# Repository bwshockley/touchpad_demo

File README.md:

# TouchPad Demo
Demo circuit board for vairous electrical touch pads.

# Why?
This is a very simple board meant to provide different methods for creating touch pads on circuit boards using various manufacturing methods via OSH Park (https://oshpark.com).

# Usage
Feel free to use or modify as you like.  Please do not sell this.

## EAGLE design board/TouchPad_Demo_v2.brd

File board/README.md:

# Eagle Files
Eagle files for schematic and the board.

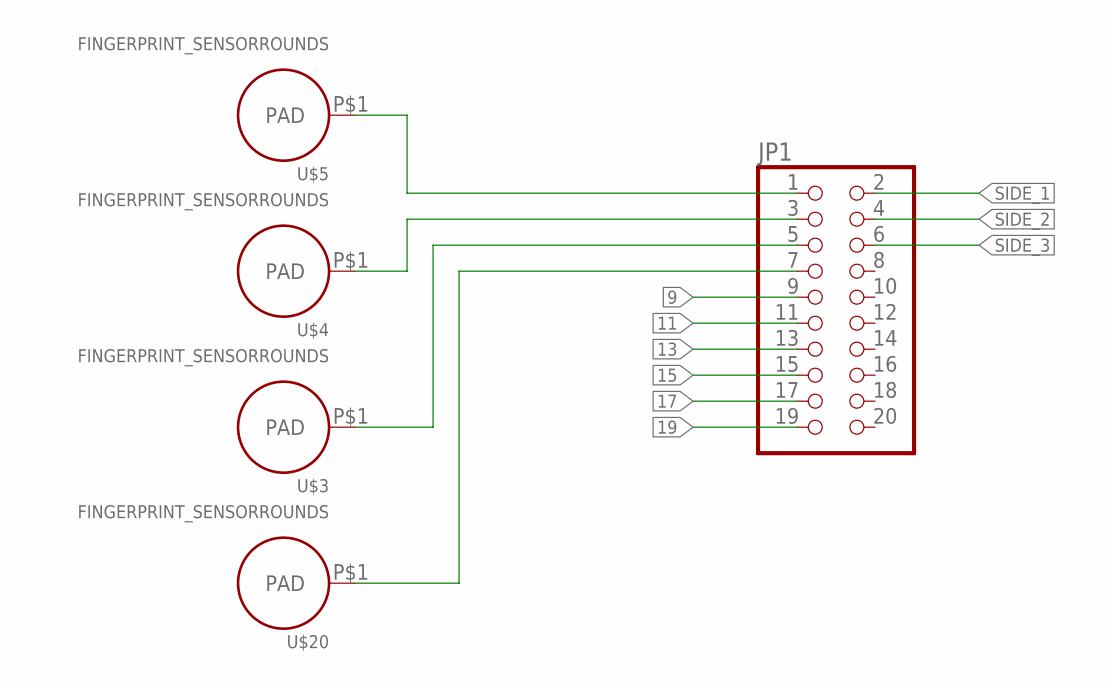
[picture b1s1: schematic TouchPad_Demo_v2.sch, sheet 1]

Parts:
JP1: HEADER-2X10MOLEX20_SIDE; MOLEX20_RIGHTANGLE
U$3, U$4, U$5, U$20: FINGERPRINT_SENSORROUNDS; FINGERPRINT_SENSOR_ROUND

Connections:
9: JP1.9
11: JP1.11
13: JP1.13
15: JP1.15
17: JP1.17
19: JP1.19
unnamed: JP1.1, U$5.P$1
unnamed: JP1.3, U$4.P$1
unnamed: JP1.5, U$3.P$1
unnamed: JP1.7, U$20.P$1
SIDE_1: JP1.2
SIDE_2: JP1.4
SIDE_3: JP1.6

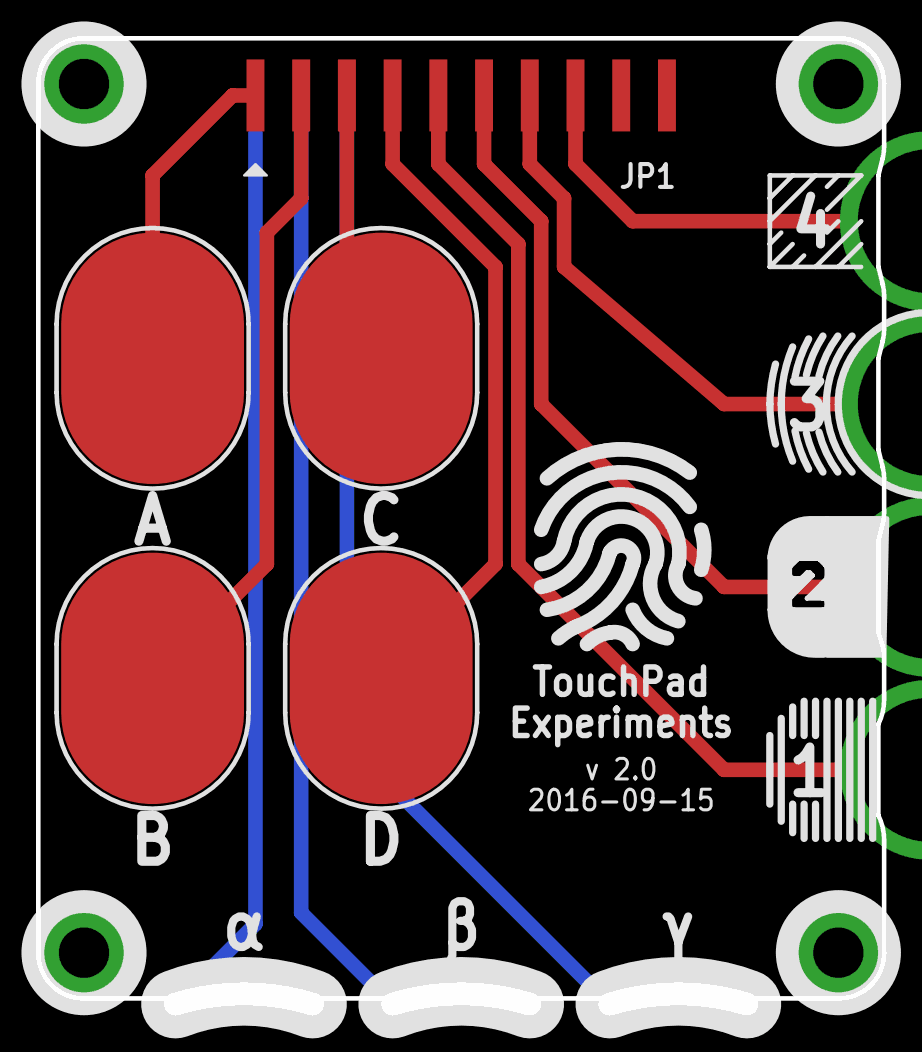
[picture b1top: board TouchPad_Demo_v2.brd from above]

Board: 2 copper layers, 46.0 x 53.1 mm, 7 parts (1 on the bottom side), 4 nets.

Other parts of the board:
U$1, U$19: FINGERPRINT

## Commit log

2016-09-16 Add v2 Schematic and Board

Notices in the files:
parts and their libraries:
microbuilder: This work is placed in the public domain, and may be freely used for commercial and non-commercial work with the following conditions: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
